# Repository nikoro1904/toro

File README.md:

# TORO

TORO is the name of my **T**ennis b**O**ll **RO**bot.

2023:

2021:

Some day in the future, TORO should be able to drive and navigate on a tennis court, search for tennis bolls, approach them, pick them up and eventually bring them back to me. It would also be nice to make TORO in a more generalistic matter so it can adapt or be adapted to different kind of bolls (such as golf bolls for example).

This repo contains general notes, electronic circuits, 3D parts and code of TORO. It is nowhere near being finished but will hopefully be some day. When this is the case, I might upload more detailed instructions on how to built TORO.

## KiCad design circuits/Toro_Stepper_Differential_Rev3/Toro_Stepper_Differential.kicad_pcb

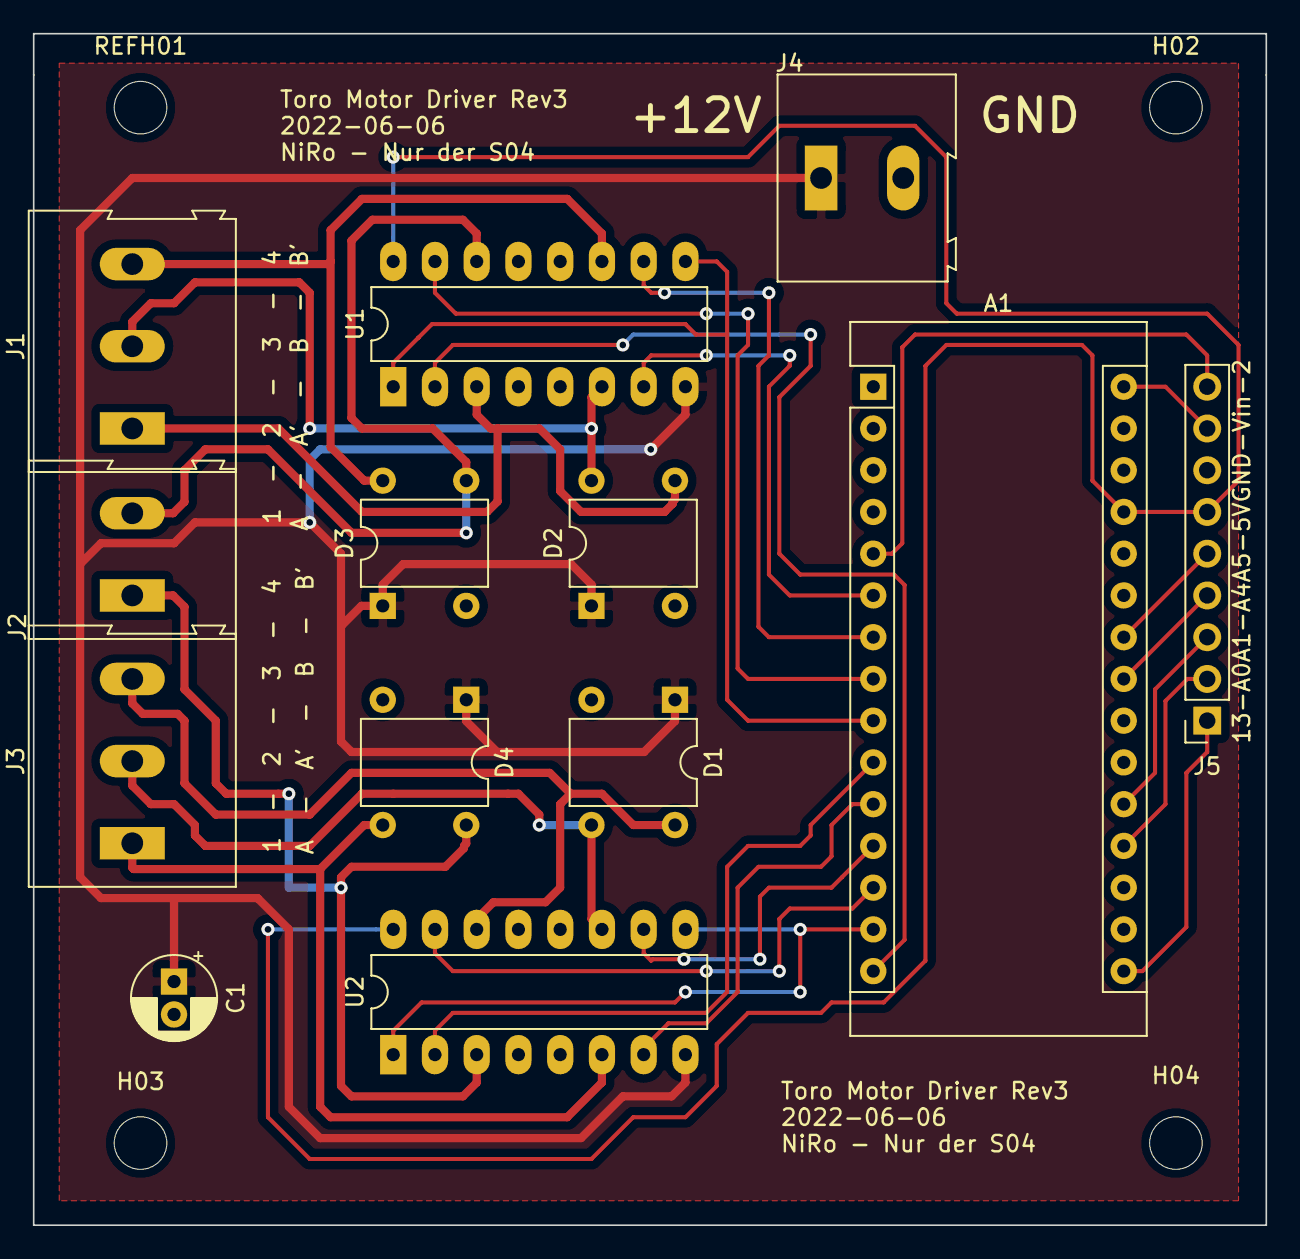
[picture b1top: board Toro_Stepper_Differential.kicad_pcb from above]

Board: 2 copper layers, 75.0 x 72.5 mm, 17 parts (0 on the bottom side), 28 nets.

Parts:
A1: Arduino_Nano_v3.x; Arduino_Nano
C1: 220nF; CP_Radial_D5.0mm_P2.00mm
D1, D2, D3, D4: D_Bridge_+-AA; BridgeRectifier_+-AA
H02, H03, H04: MountingHole_3.2mm_M3_ISO14580
J1, J3: Screw_Terminal_01x03; TerminalBlock_Altech_AK300-3_P5.00mm
J2: Screw_Terminal_01x02; TerminalBlock_Altech_AK300-2_P5.00mm
J4: Screw_Terminal _01x02; TerminalBlock_Altech_AK300-2_P5.00mm
J5: Conn_01x09_Male; PinSocket_1x09_P2.54mm_Vertical
REFH01: MountingHole_3.2mm_M3_ISO14580
U1, U2: L293; DIP-16_W7.62mm_LongPads

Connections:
+10V: C1.1, D1.1, D2.1, D3.1, D4.1, J4.1, U1.8, U2.8
GND: A1.4, A1.29, C1.2, D1.2, D2.2, D3.2, D4.2, J4.2, J5.7, U1.4, U1.5, U1.12, U1.13, U2.4, U2.5, U2.12, U2.13
unnamed: A1.5, J5.9
unnamed: A1.6, U1.7
unnamed: A1.7, U1.10
unnamed: A1.8, U1.15
unnamed: A1.9, U1.1, U1.9
unnamed: A1.10, U2.2
unnamed: A1.11, U2.7
unnamed: A1.12, U2.10
unnamed: A1.13, U2.15
unnamed: A1.14, U2.1, U2.9
unnamed: A1.15, U1.2
unnamed: A1.16, J5.1
unnamed: A1.19, J5.2
unnamed: A1.20, J5.3
unnamed: A1.23, J5.4
unnamed: A1.24, J5.5
unnamed: A1.27, J5.6, U1.16, U2.16
unnamed: A1.30, J5.8
unnamed: D1.3, J3.2, U2.11
unnamed: D1.4, J3.3, U2.14
unnamed: D2.3, J1.1, U1.3
unnamed: D2.4, J1.2, U1.6
unnamed: D3.3, J2.2, U1.14
unnamed: D3.4, J1.3, U1.11
unnamed: D4.3, J3.1, U2.6
unnamed: D4.4, J2.1, U2.3

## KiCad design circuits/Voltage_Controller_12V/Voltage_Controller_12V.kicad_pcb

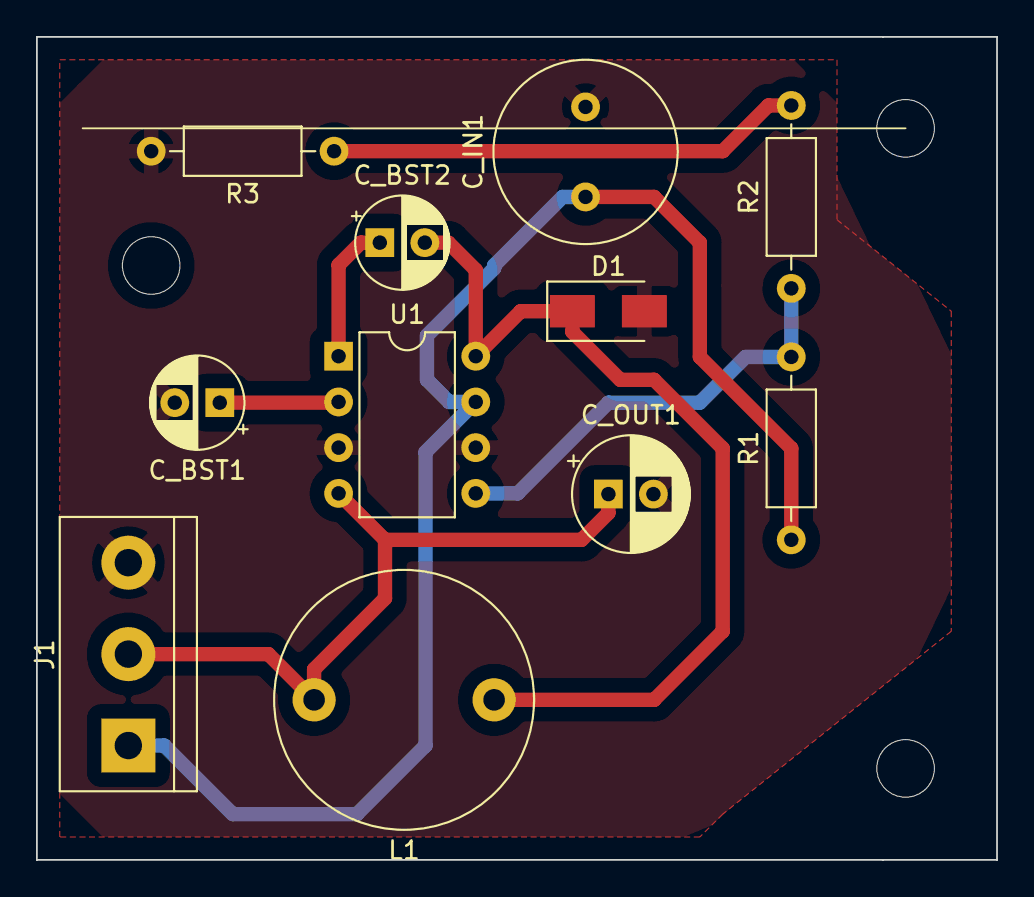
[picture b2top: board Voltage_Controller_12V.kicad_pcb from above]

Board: 2 copper layers, 53.3 x 45.7 mm, 11 parts (0 on the bottom side), 8 nets.

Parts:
C_BST1, C_BST2: 0.1µF Tantal; CP_Radial_D5.0mm_P2.50mm
C_IN1: 220µF ELKO; C_Radial_D10.0mm_H16.0mm_P5.00mm
C_OUT1: 15µF Tantal; CP_Radial_D6.3mm_P2.50mm
D1: MBRA 340T3G ONS; D_SMA
J1: Screw_Terminal_01x03; TerminalBlock_bornier-3_P5.08mm
L1: 220µH; L_Radial_D14.2mm_P10.00mm_Neosid_SD14
R1: 1M; R_Axial_DIN0207_L6.3mm_D2.5mm_P10.16mm_Horizontal
R2: 100K; R_Axial_DIN0207_L6.3mm_D2.5mm_P10.16mm_Horizontal
R3: 47K; R_Axial_DIN0207_L6.3mm_D2.5mm_P10.16mm_Horizontal
U1: MAX5035CUPA; DIP-8_W7.62mm

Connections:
+12V: C_OUT1.1, J1.2, L1.2, U1.4
GND: C_BST1.2, C_IN1.2, C_OUT1.2, D1.2, J1.3, R3.2, U1.3, U1.6
unnamed: C_BST1.1, U1.2
unnamed: C_BST2.1, U1.1
unnamed: C_BST2.2, D1.1, L1.1, U1.8
unnamed: R1.2, R2.1, U1.5
unnamed: R2.2, R3.1
Vdrive: C_IN1.1, J1.1, R1.1, U1.7

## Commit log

2021-08-08 write readme
2021-08-08 add image of toro
2021-08-08 change image to smaller resolution
2021-08-08 change image to smaller resolution again
2021-08-08 added old files
2021-08-28 added new circuit
2021-10-01 made bluetooth connection work
2022-01-05 added more commands
2022-05-26 formatting
2022-06-04 added rev2 and rev3 with diodes and bridge rectifier, respectively
2022-07-21 stepper test
2022-07-21 fixed oscillations for turn_right
2022-07-21 added excel for hardware connections
2022-08-29 created venv for opencv dev
2022-08-29 test scripts for ball tracking
2022-08-30 removed unnecessary stuff
2022-09-09 flip image
2022-09-10 installed pygame in venv
2022-09-10 added direction vizualization
2022-09-10 exclude venv folder
2022-09-10 removed venv from git tracking
2022-09-11 try new approach for keyboard control
2022-09-12 added and removed changes for i2c msg handling
2023-11-11 new variant for serial comm
2023-11-12 fix serial communication
2023-11-26 added serial init handshake for motor driver module
2023-11-26 new image of TORO
2023-11-26 first steps for remote control of motors
